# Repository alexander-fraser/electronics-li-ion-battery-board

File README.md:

# electronics-li-ion-battery-board
A protected li-ion battery board to connect 18650 cells to projects.

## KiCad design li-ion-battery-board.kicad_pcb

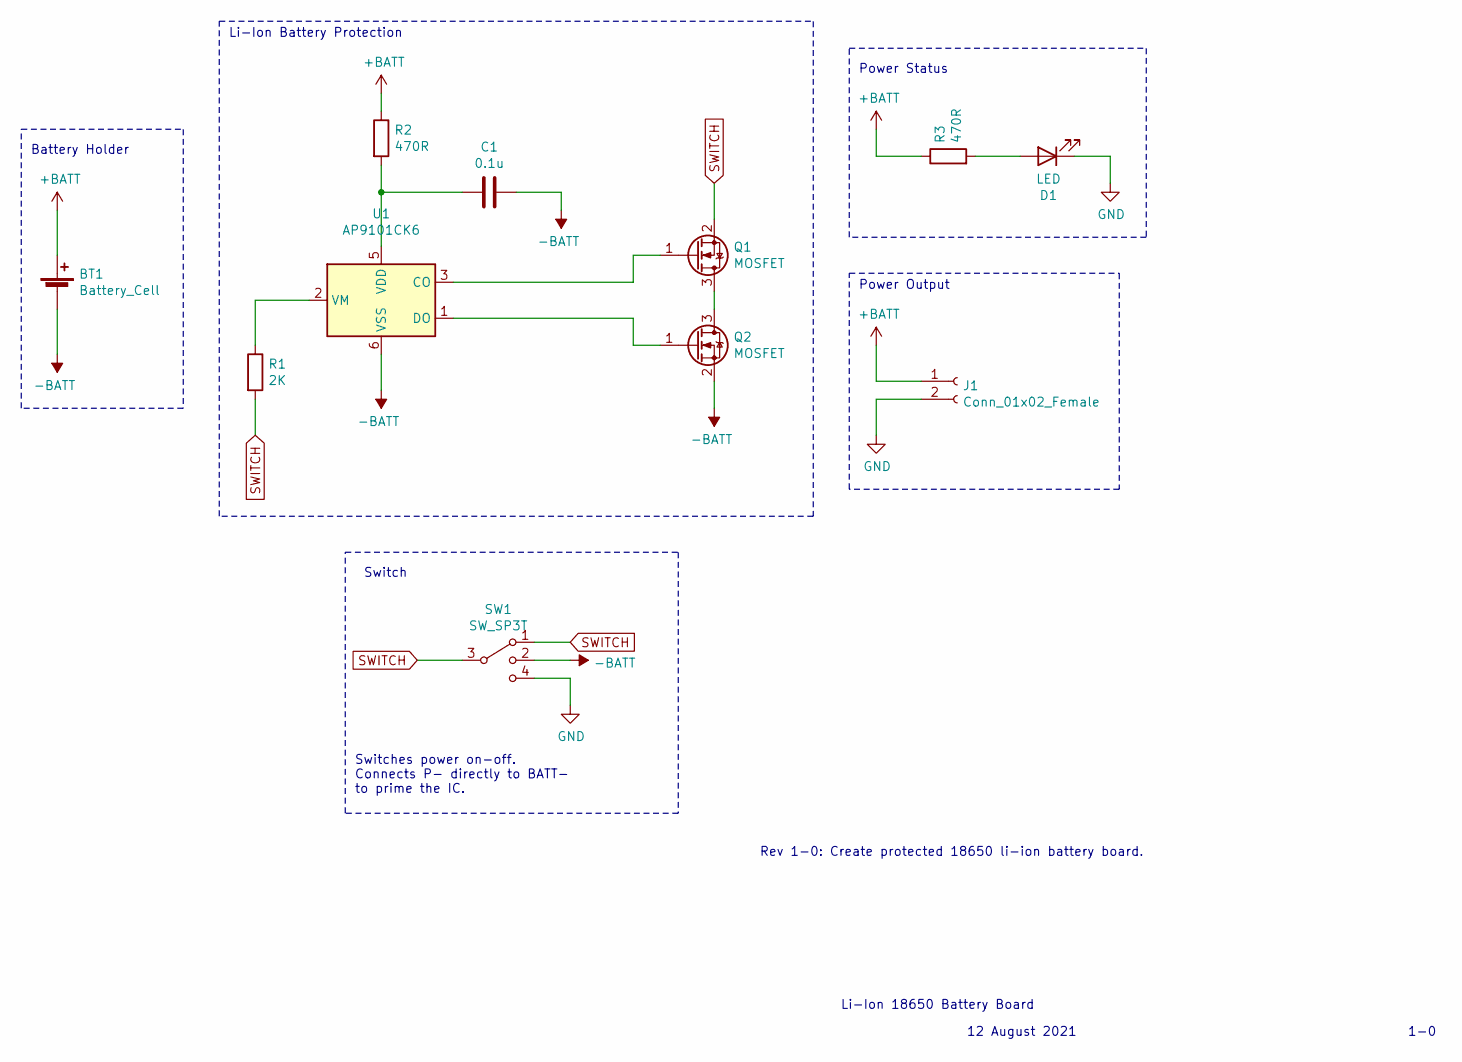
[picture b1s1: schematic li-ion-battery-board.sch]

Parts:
BT1: Battery_Cell; BatteryHolder_CZK_1x18650
C1: 0.1u; C_1206_3216Metric_Pad1.33x1.80mm_HandSolder
D1: LED; LED_1206_3216Metric_Castellated
J1: Conn_01x02_Female; Castellation_1x02_P2.54mm_Vertical
Q1, Q2: MOSFET; SOT-23
R1: 2K; R_1206_3216Metric_Pad1.30x1.75mm_HandSolder
R2, R3: 470R; R_1206_3216Metric_Pad1.30x1.75mm_HandSolder
SW1: SW_SP3T; SW_SP3T_Nidec_CL_SB_13B
U1: AP9101CK6; SOT-23-6

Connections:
+BATT: BT1.1 (+), J1.1, R2.1, R3.1
-BATT: BT1.2 (-), C1.1, Q2.2 (S), SW1.2, U1.6 (VSS)
GND: D1.1 (K), J1.2, SW1.4
unnamed: C1.2, R2.2, U1.5 (VDD)
unnamed: D1.2 (A), R3.2
unnamed: Q1.1 (G), U1.3 (CO)
unnamed: Q1.3 (D), Q2.3 (D)
unnamed: Q2.1 (G), U1.1 (DO)
unnamed: R1.1, U1.2 (VM)
SWITCH: Q1.2 (S), R1.2, SW1.1, SW1.3

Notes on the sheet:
Li-Ion 18650 Battery Board
12 August 2021
1-0
Rev 1-0: Create protected 18650 li-ion battery board.
Li-Ion Battery Protection
Power Status
Power Output
Switch
Battery Holder
Switches power on-off. Connects P- directly to BATT- to prime the IC.

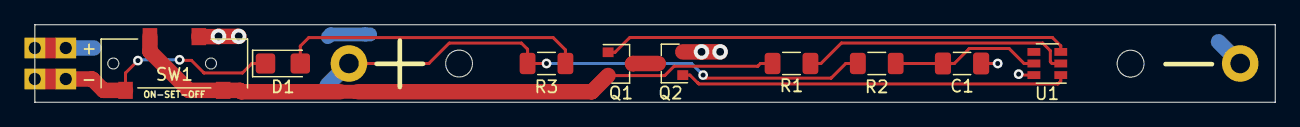
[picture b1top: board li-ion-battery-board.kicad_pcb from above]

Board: 2 copper layers, 101.6 x 6.4 mm, 13 parts (1 on the bottom side), 10 nets.

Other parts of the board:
M1, M1#2: MountingHole_2.2mm_M2

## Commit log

2021-08-13 Create electrical schematic.
2021-08-14 Assign footprints in schematic.
2021-08-16 Change MOSFET pin and layout assignments.
2021-08-16 Complete PCB layout.
2021-08-17 Add mounting holes and modify silkscreen text.
2021-08-17 Generate plots.
2021-08-17 Correct solder mask for castellations.
